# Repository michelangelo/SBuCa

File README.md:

# SBuCa

### Overview
**SBuCa** stands for Smart Business card and it's a card-sized, e-ink based, embedded platform.

### Goals of the project

Its high-level goal is to provide a reference platform for e-ink based display applications and there's nothing better than a business card for that!

Other than that, these are the main goals:

* Completely open source
* Vertical: everything has to be done in house
* Easy to carry along (it's a business card)
* Energy efficient: it's powered by two CR-2032

Everything in **SBuCa is open source**, starting with its hardware design: schematics and layout are provided along with the whole KiCad project, including eventual custom footprints.

### Cumae: SBuCa's proto-OS/firmware
As already pointed out, one of the non-functional goals of SBuCa, since its inception, was to come up with something vertical, meaning that everything had to be done from scratch, even its OS/firmware.

This goal has been achieved by **Cumae**, the proto-OS SBuCa is currently running.

Cumae, like everything else here, is totally open source and can be found on [its own repository](https://github.com/michelangelo/Cumae).

### How does it look like?

Well, it's a *business* card and it looks like this:

### BOM

*WIP*

### Other revisions

This repository starts tracking from the LV (*Line Verification*) revision; previous revisions (B0, B1 aka "the wingboard") are not available just yet on this repository.
If you really need them just shoot the author an email.

### Author

The original author is *Michelangelo De Simone*, a system software engineer that is always open to thinker and hack around with the ultimate goal of *learning stuff, breaking things: it's the family business*. ;-)

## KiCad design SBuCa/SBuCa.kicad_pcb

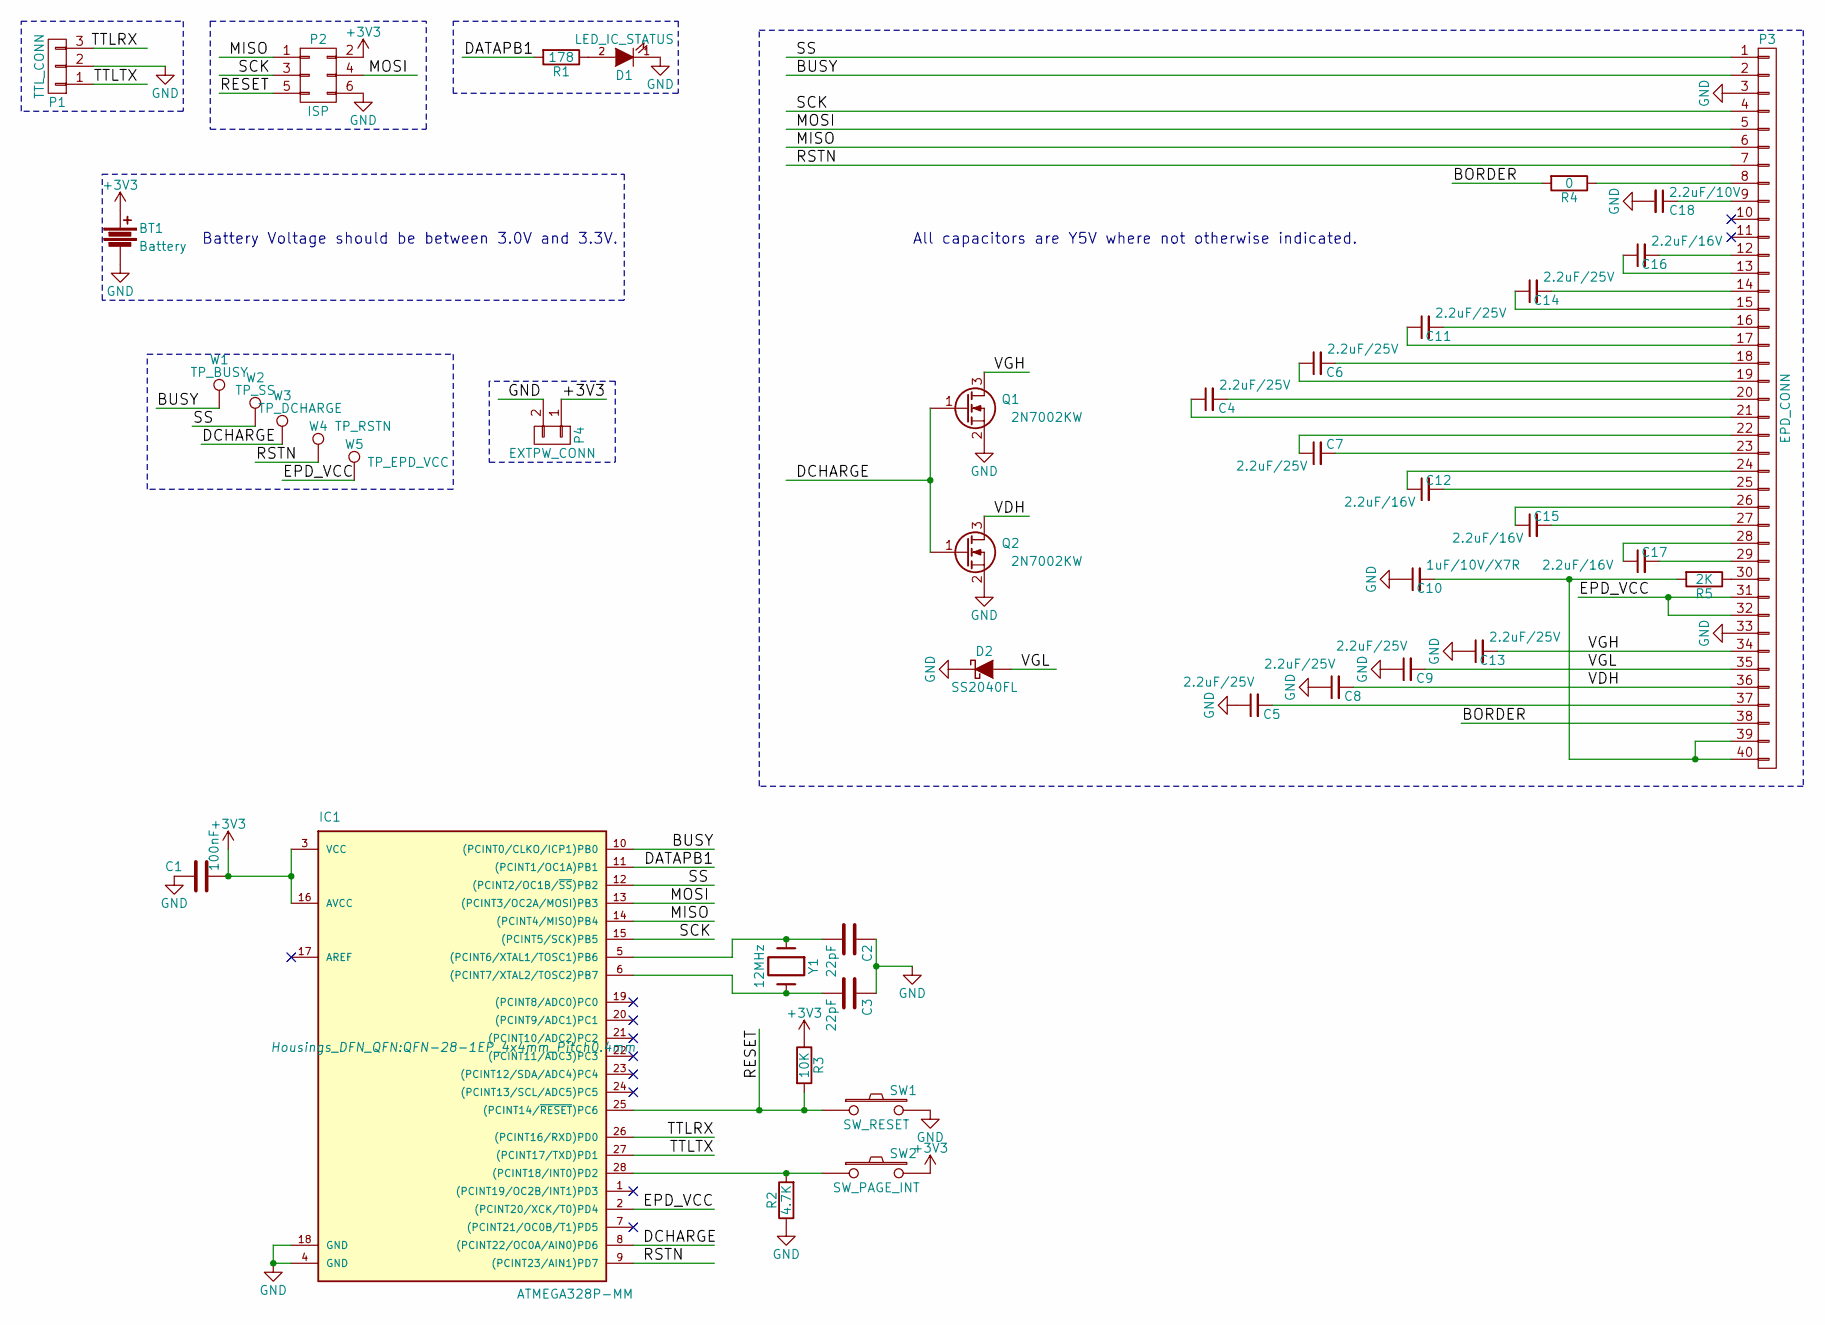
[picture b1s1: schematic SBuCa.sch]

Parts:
BT1: Battery; SBuCa_CR2032_Holder
C1: 100nF; C_0603
C2, C3: 22pF; C_0603
C4, C5, C6, C7, C8, C9, C11, C13, C14: 2.2uF/25V; C_0603
C10: 1uF/10V/X7R; C_0603
C12, C15, C16, C17: 2.2uF/16V; C_0603
C18: 2.2uF/10V; C_0603
D1: LED_IC_STATUS; LED_0603
D2: SS2040FL; SOD-123
IC1: ATMEGA328P-MM; QFN-28-1EP_4x4mm_Pitch0.4mm
P1: TTL_CONN; Pin_Header_Straight_1x03
P2: ISP; Pin_Header_Straight_2x03
P3: EPD_CONN; SBuCa_FH28_40_05mmpitch
P4: EXTPW_CONN; Pin_Header_Straight_1x02_Pitch2.54mm
Q1, Q2: 2N7002KW; SOT-323
R1: 178; R_0603
R2: 4.7K; R_0603
R3: 10K; R_0603
R4: 0; R_0603
R5: 2K; R_0603
SW1: SW_RESET; SW_SPST_KMR2
SW2: SW_PAGE_INT; SW_SPST_B3S-1000
W1: TP_BUSY; Measurement_Point_Round-SMD-Pad_Small
W2: TP_SS; Measurement_Point_Round-SMD-Pad_Small
W3: TP_DCHARGE; Measurement_Point_Round-SMD-Pad_Small
W4: TP_RSTN; Measurement_Point_Round-SMD-Pad_Small
W5: TP_EPD_VCC; Measurement_Point_Round-SMD-Pad_Small
Y1: 12MHz; Crystal_SMD_5032_2Pads

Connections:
+3V3: BT1.1, C1.2, IC1.3 (VCC), IC1.16 (AVCC), P2.2, P4.1, R3.1, SW2.2; also elsewhere on the board
/BORDER: P3.38, R4.2
/BUSY: IC1.10 ((PCINT0/CLKO/ICP1)PB0), P3.2, W1.1
/DATAPB1: IC1.11 ((PCINT1/OC1A)PB1), R1.2
/DCHARGE: IC1.8 ((PCINT22/OC0A/AIN0)PD6), Q1.1 (G), Q2.1 (G), W3.1
/EPD_VCC: IC1.2 ((PCINT20/XCK/T0)PD4), P3.31, P3.32, W5.1
/MISO: IC1.14 ((PCINT4/MISO)PB4), P2.1, P3.6
/MOSI: IC1.13 ((PCINT3/OC2A/MOSI)PB3), P2.4, P3.5
/RESET: IC1.25 ((PCINT14/~RESET~)PC6), P2.5, R3.2, SW1.1
/RSTN: IC1.9 ((PCINT23/AIN1)PD7), P3.7, W4.1
/SCK: IC1.15 ((PCINT5/SCK)PB5), P2.3, P3.4
/SS: IC1.12 ((PCINT2/OC1B/~SS~)PB2), P3.1, W2.1
/TTLRX: IC1.26 ((PCINT16/RXD)PD0), P1.3
/TTLTX: IC1.27 ((PCINT17/TXD)PD1), P1.1
/VDH: C8.2, P3.36, Q2.3 (D)
/VGH: C13.2, P3.34, Q1.3 (D)
/VGL: C9.2, D2.2 (A), P3.35
GND: BT1.2, C1.1, C2.1, C3.1, C5.1, C8.1, C9.1, C10.1, C13.1, C18.2, D1.1 (K), D2.1 (K), IC1.4 (GND), IC1.18 (GND), P1.2, P2.6, P3.3, P3.33, P4.2, Q1.2 (S), Q2.2 (S), R2.1, SW1.2; also elsewhere on the board
unnamed: C2.2, IC1.5 ((PCINT6/XTAL1/TOSC1)PB6), Y1.1
unnamed: C3.2, IC1.6 ((PCINT7/XTAL2/TOSC2)PB7), Y1.2
unnamed: C4.1, P3.21
unnamed: C4.2, P3.20
unnamed: C5.2, P3.37
unnamed: C6.1, P3.19
unnamed: C6.2, P3.18
unnamed: C7.1, P3.22
unnamed: C7.2, P3.23
unnamed: C10.2, P3.39, P3.40, R5.2
unnamed: C11.1, P3.17
unnamed: C11.2, P3.16
unnamed: C12.1, P3.24
unnamed: C12.2, P3.25
unnamed: C14.1, P3.15
unnamed: C14.2, P3.14
unnamed: C15.1, P3.26
unnamed: C15.2, P3.27
unnamed: C16.1, P3.13
unnamed: C16.2, P3.12
unnamed: C17.1, P3.28
unnamed: C17.2, P3.29
unnamed: C18.1, P3.9
unnamed: D1.2 (A), R1.1
unnamed: IC1.28 ((PCINT18/INT0)PD2), R2.2, SW2.1
unnamed: P3.8, R4.1
unnamed: P3.30, R5.1

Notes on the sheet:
All capacitors are Y5V where not otherwise indicated.
Battery Voltage should be between 3.0V and 3.3V.

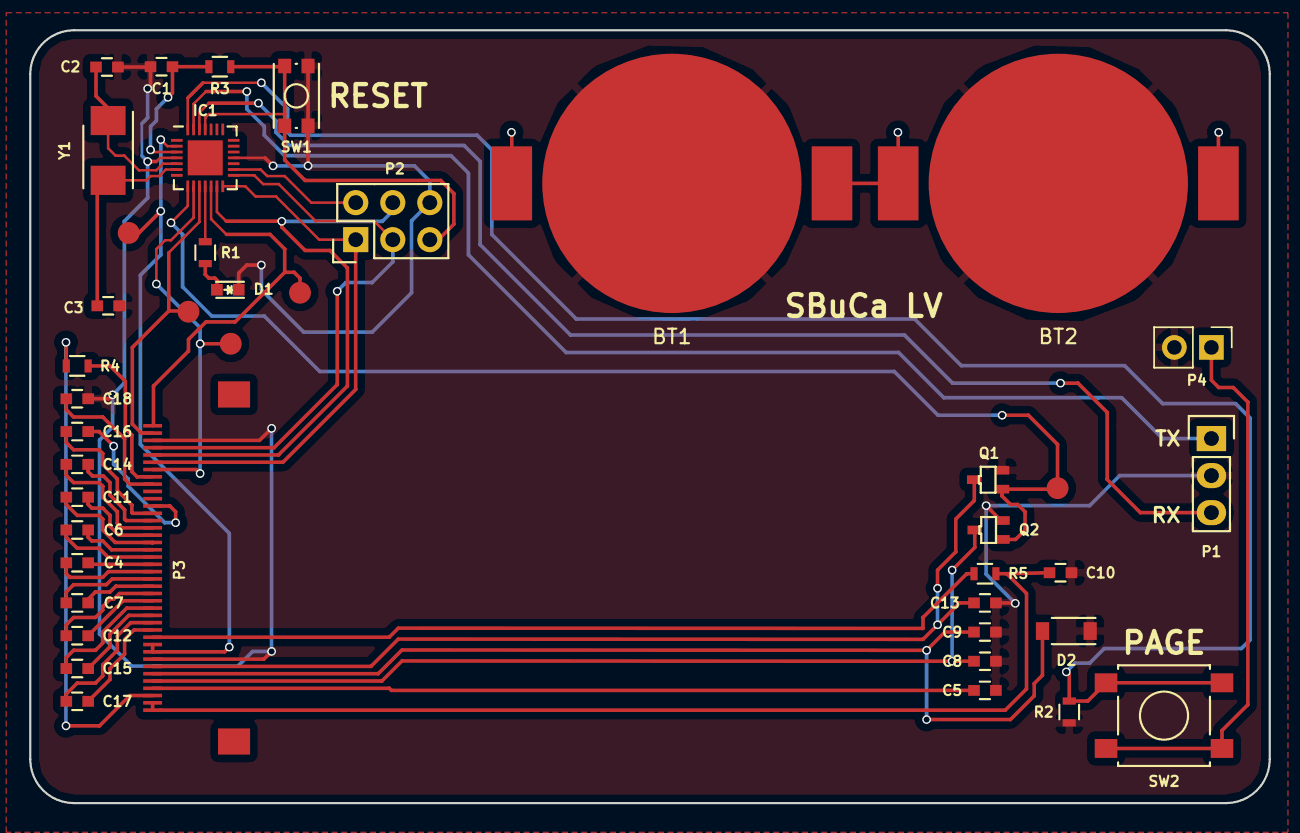
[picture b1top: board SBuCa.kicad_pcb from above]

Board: 2 copper layers, 85.0 x 53.0 mm, 42 parts (0 on the bottom side), 45 nets.

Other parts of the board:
BT2: Battery; SBuCa_CR2032_Holder

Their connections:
+3V3: BT2.1; also elsewhere on the board
GND: BT2.2; also elsewhere on the board

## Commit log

2017-06-19 SBuCA LV designs, documentation and pics.
2017-06-19 README.md: updated with pics.
2017-12-31 Update README.md
    Link fix.
